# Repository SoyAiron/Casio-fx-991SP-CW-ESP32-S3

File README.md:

# Casio fx-991SP CW + ESP32-S3

# Casio fx-991SP CW

Este es un proyecto que he decidido hacer en mis tiempos libres de 2º Bachillerato.
Consistira en modificar una Casio fx-991SP CW para quedarnos con la carcasa y darle mas potencia mediante un ESP32-S3, tendra una mejor pantalla, calculo avanzado y conectividad wifi.

Esta pensado para ser **100% reversible**. La placa original de Casio se conserva intacta y la carcasa exterior de plástico no sufre ningún corte, agujero ni modificación destructiva.

## Arquitectura de Hardware
* **Microcontrolador:** ESP32-S3-MINI-1 (Wi-Fi, Dual Core).
* **Pantalla:** OLED 2.08" Monocromática.
* **Alimentación:** Batería LiPo 3.7V con gestor de carga TP4054 y LDO ME6211.
* **PCB:** Diseño personalizado (KiCad) con contactos de membrana en oro inmerso (ENIG).

## Estructura del Repositorio
* `/Hardware`: Archivos de diseño electrónico y PCB desarrollados en KiCad 8.
* `/Firmware`: Código fuente en C++ estructurado para PlatformIO.
* `/Docs`: Datasheets, fotografías del proceso y documentación técnica.

## Licencia
Este proyecto se distribuye bajo la licencia **Creative Commons Reconocimiento-NoComercial 4.0 (CC BY-NC 4.0)**. Eres libre de estudiar, copiar y modificar el diseño para fines educativos o personales. El uso comercial o la venta de este dispositivo requiere autorización expresa del autor.

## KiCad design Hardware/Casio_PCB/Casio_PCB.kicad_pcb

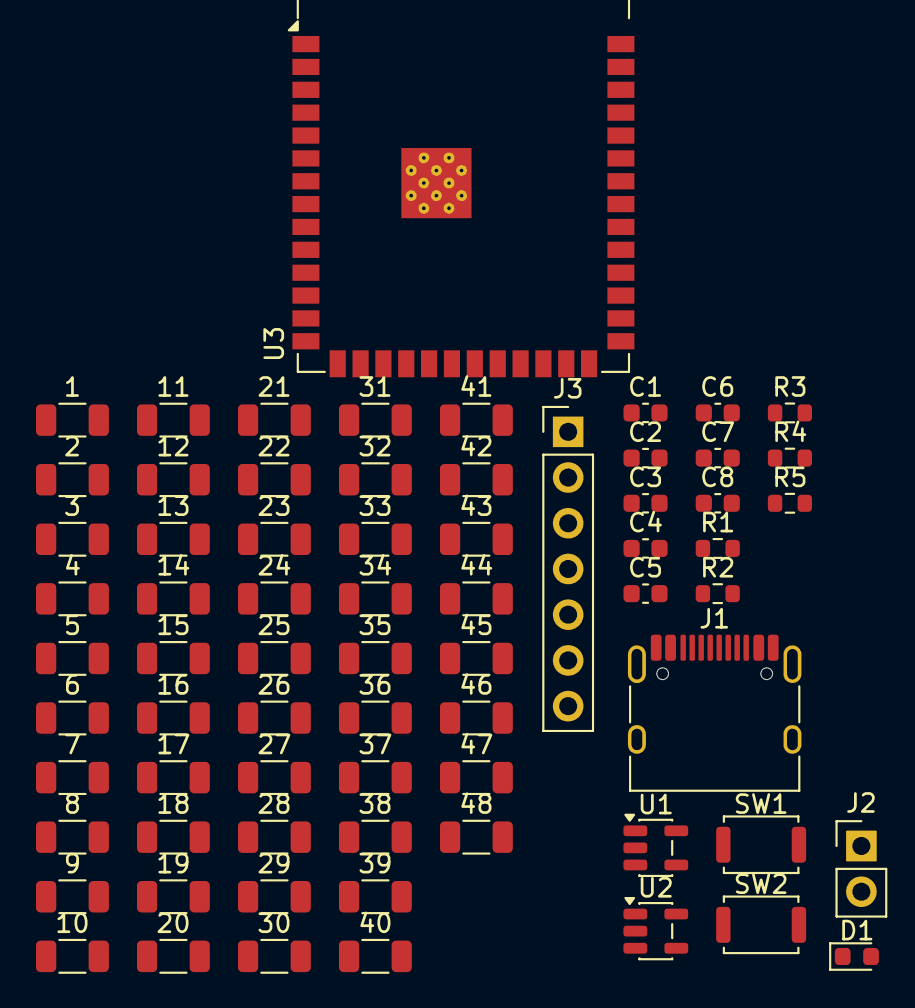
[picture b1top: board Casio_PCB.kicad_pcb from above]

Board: 2 copper layers, 70 parts (0 on the bottom side), 33 nets, no tracks yet.

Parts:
C1, C2, C3: 4.7uF; C_0603_1608Metric
C4, C5, C8: 1uF; C_0603_1608Metric
C6: 10uF; C_0603_1608Metric
C7: 0.1uF; C_0603_1608Metric
D1: LED; LED_0603_1608Metric
J1: USB_C_Receptacle_USB2.0_16P; USB_C_Receptacle_HRO_TYPE-C-31-M-12
J2: Conn_01x02; PinHeader_1x02_P2.54mm_Vertical
J3: OLED_SCREEN; PinHeader_1x07_P2.54mm_Vertical
R1, R2: 5.1k; R_0603_1608Metric
R3, R5: 10k; R_0603_1608Metric
R4: 1k; R_0603_1608Metric
SW1: RESET; SW_Push_SPST_NO_Alps_SKRK
SW2: BOOT; SW_Push_SPST_NO_Alps_SKRK
U1: MCP73831-2-OT; SOT-23-5
U2: AP2112K-3.3; SOT-23-5
U3: ESP32-S3-WROOM-1-N8; ESP32-S3-WROOM-1
 1,  2,  3,  4,  5,  6,  7,  8,  9,  10,  11,  12,  13,  14,  15,  16,  17,  18,  19,  20,  21,  22,  23,  24,  25,  26,  27,  28,  29,  30,  31,  32,  33,  34,  35,  36,  37,  38,  39,  40,  41,  42,  43,  44,  45,  46,  47,  48: R_1206_3216Metric

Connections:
+3V3: C5.1, C6.1, C7.1, J3.2, R5.1, U2.5 (VOUT), U3.2 (3V3)
+5V: C1.1, C2.1, J1.A4 (VBUS), J1.A9 (VBUS), J1.B4 (VBUS), J1.B9 (VBUS), R4.2, U1.4 (V_{DD})
/C1: U3.39 (IO1), 1.2, 2.2, 3.2, 4.2, 5.2, 6.2, 7.2, 8.2, 9.2
/C2: U3.38 (IO2), 10.2, 11.2, 12.2, 13.2, 14.2, 15.2, 16.2, 17.2, 18.2
/C3: U3.15 (IO3), 19.2, 20.2, 21.2, 22.2, 23.2, 24.2, 25.2, 26.2
/C4: U3.4 (IO4), 27.2, 28.2, 29.2, 30.2, 31.2, 32.2, 33.2, 34.2, 35.2
/C5: U3.5 (IO5), 36.2, 37.2, 38.2, 39.2, 40.2, 41.2, 42.2, 43.2
/C6: U3.6 (IO6), 44.2, 45.2, 46.2, 47.2, 48.2
/F1: U3.21 (IO13), 1.1, 10.1, 27.1, 44.1
/F2: U3.22 (IO14), 2.1, 11.1, 19.1, 28.1, 36.1, 45.1
/F3: U3.8 (IO15), 3.1, 12.1, 20.1, 29.1, 37.1, 46.1
/F4: U3.9 (IO16), 4.1, 13.1, 21.1, 30.1, 38.1, 47.1
/F5: U3.10 (IO17), 5.1, 14.1, 22.1, 31.1, 39.1, 48.1
/F6: U3.11 (IO18), 6.1, 15.1, 23.1, 32.1, 40.1
/F7: U3.7 (IO7), 7.1, 16.1, 24.1, 33.1, 41.1
/F8: U3.23 (IO21), 8.1, 17.1, 25.1, 34.1, 42.1
/F9: U3.33 (IO40), 9.1, 18.1, 26.1, 35.1, 43.1
/OLED_CS: J3.7, U3.12 (IO8)
/OLED_DC: J3.6, U3.17 (IO9)
/OLED_MOSI: J3.4, U3.19 (IO11)
/OLED_RES: J3.5, U3.18 (IO10)
/OLED_SCK: J3.3, U3.20 (IO12)
/USB_D+: J1.A6 (D+), J1.B6 (D+), U3.14 (USB_D+)
/USB_D-: J1.A7 (D-), J1.B7 (D-), U3.13 (USB_D-)
/VBAT: C3.1, C4.1, J2.1, U1.3 (V_{BAT}), U2.1 (VIN), U2.3 (EN)
GND: C1.2, C2.2, C3.2, C4.2, C5.2, C6.2, C7.2, C8.2, J1.A1 (GND), J1.A12 (GND), J1.B1 (GND), J1.B12 (GND), J1.SH (SHIELD), J2.2, J3.1, R1.1, R2.2, R3.2, SW1.1, SW2.1, U1.2 (V_{SS}), U2.2 (GND), U3.1 (GND), U3.40 (GND), U3.41 (GND)
unnamed: D1.2 (A), R4.1
unnamed: D1.1 (K), U1.1 (STAT)
unnamed: J1.A5 (CC1), R1.2
unnamed: J1.B5 (CC2), R2.1
unnamed: R3.1, U1.5 (PROG)
unnamed: C8.1, R5.2, SW1.2, U3.3 (EN)
unnamed: SW2.2, U3.27 (IO0)
